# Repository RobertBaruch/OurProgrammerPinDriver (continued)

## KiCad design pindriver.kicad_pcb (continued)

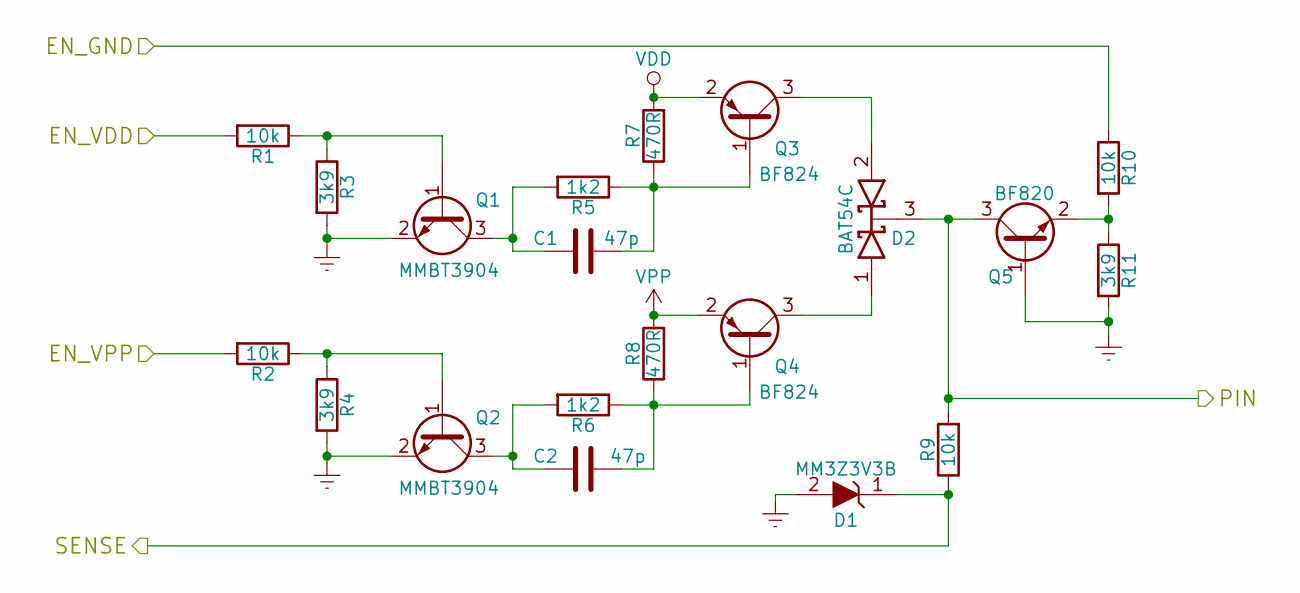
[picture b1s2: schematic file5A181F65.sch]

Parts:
C1, C2: 47p; C_0603_HandSoldering
D1: MM3Z3V3B; D_SOD-323_HandSoldering
D2: BAT54C; SOT-23_Handsoldering
Q1, Q2: MMBT3904; SOT-23_Handsoldering
Q3, Q4: BF824; SOT-23_Handsoldering
Q5: BF820; SOT-23_Handsoldering
R1, R2, R9, R10: 10k; R_0603_HandSoldering
R3, R4, R11: 3k9; R_0603_HandSoldering
R5, R6: 1k2; R_0603_HandSoldering
R7, R8: 470R; R_0603_HandSoldering

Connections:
/EN_GND36: R10.1; also elsewhere on the board
/EN_VDD36: R1.2; also elsewhere on the board
/EN_VPP36: R2.2; also elsewhere on the board
/PIN36: D2.3 (K), Q5.3 (C), R9.2; also elsewhere on the board
/SENSE36: D1.1 (K), R9.1; also elsewhere on the board
GNDREF: D1.2 (A), Q1.2 (E), Q2.2 (E), Q5.1 (B), R3.2, R4.2, R11.2; also elsewhere on the board
unnamed: C1.1, Q3.1 (B), R5.1, R7.1
unnamed: C1.2, Q1.3 (C), R5.2
unnamed: C2.1, Q4.1 (B), R6.1, R8.1
unnamed: C2.2, Q2.3 (C), R6.2
unnamed: D2.1 (A), Q4.3 (C)
unnamed: D2.2 (A), Q3.3 (C)
unnamed: Q1.1 (B), R1.1, R3.1
unnamed: Q2.1 (B), R2.1, R4.1
unnamed: Q5.2 (E), R10.2, R11.1
VDD: Q3.2 (E), R7.2; also elsewhere on the board
VPP: Q4.2 (E), R8.2; also elsewhere on the board

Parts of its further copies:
C3, C4, C5, C6, C7, C8, C9, C10, C11, C12, C13, C14, C15, C16, C17, C18, C19, C20, C21, C22, C23, C24, C25, C26, C27, C28, C29, C30, C31, C32, C33, C34, C35, C36, C37, C38, C39, C40, C41, C42, C43, C44, C45, C46, C47, C48, C49, C50, C51, C52, C53, C54, C55, C56, C57, C58, C59, C60, C61, C62, C63, C64, C65, C66, C67, C68, C69, C70, C71, C72, C73, C74, C75, C76, C77, C78, C79, C80: 47p; C_0603_HandSoldering
D3, D5, D7, D9, D11, D13, D15, D17, D19, D21, D23, D25, D27, D29, D31, D33, D35, D37, D39, D41, D43, D45, D47, D49, D51, D53, D55, D57, D59, D61, D63, D65, D67, D69, D71, D73, D75, D77, D79: MM3Z3V3B; D_SOD-323_HandSoldering
D4, D6, D8, D10, D12, D14, D16, D18, D20, D22, D24, D26, D28, D30, D32, D34, D36, D38, D40, D42, D44, D46, D48, D50, D52, D54, D56, D58, D60, D62, D64, D66, D68, D70, D72, D74, D76, D78, D80: BAT54C; SOT-23_Handsoldering
Q6, Q7, Q11, Q12, Q16, Q17, Q21, Q22, Q26, Q27, Q31, Q32, Q36, Q37, Q41, Q42, Q46, Q47, Q51, Q52, Q56, Q57, Q61, Q62, Q66, Q67, Q71, Q72, Q76, Q77, Q81, Q82, Q86, Q87, Q91, Q92, Q96, Q97, Q101, Q102, Q106, Q107, Q111, Q112, Q116, Q117, Q121, Q122, Q126, Q127, Q131, Q132, Q136, Q137, Q141, Q142, Q146, Q147, Q151, Q152, Q156, Q157, Q161, Q162, Q166, Q167, Q171, Q172, Q176, Q177, Q181, Q182, Q186, Q187, Q191, Q192, Q196, Q197: MMBT3904; SOT-23_Handsoldering
Q8, Q9, Q13, Q14, Q18, Q19, Q23, Q24, Q28, Q29, Q33, Q34, Q38, Q39, Q43, Q44, Q48, Q49, Q53, Q54, Q58, Q59, Q63, Q64, Q68, Q69, Q73, Q74, Q78, Q79, Q83, Q84, Q88, Q89, Q93, Q94, Q98, Q99, Q103, Q104, Q108, Q109, Q113, Q114, Q118, Q119, Q123, Q124, Q128, Q129, Q133, Q134, Q138, Q139, Q143, Q144, Q148, Q149, Q153, Q154, Q158, Q159, Q163, Q164, Q168, Q169, Q173, Q174, Q178, Q179, Q183, Q184, Q188, Q189, Q193, Q194, Q198, Q199: BF824; SOT-23_Handsoldering
Q10, Q15, Q20, Q25, Q30, Q35, Q40, Q45, Q50, Q55, Q60, Q65, Q70, Q75, Q80, Q85, Q90, Q95, Q100, Q105, Q110, Q115, Q120, Q125, Q130, Q135, Q140, Q145, Q150, Q155, Q160, Q165, Q170, Q175, Q180, Q185, Q190, Q195, Q200: BF820; SOT-23_Handsoldering
R12, R13, R20, R21, R23, R24, R31, R32, R34, R35, R42, R43, R45, R46, R53, R54, R56, R57, R64, R65, R67, R68, R75, R76, R78, R79, R86, R87, R89, R90, R97, R98, R100, R101, R108, R109, R111, R112, R119, R120, R122, R123, R130, R131, R133, R134, R141, R142, R144, R145, R152, R153, R155, R156, R163, R164, R166, R167, R174, R175, R177, R178, R185, R186, R188, R189, R196, R197, R199, R200, R207, R208, R210, R211, R218, R219, R221, R222, R229, R230, R232, R233, R240, R241, R243, R244, R251, R252, R254, R255, R262, R263, R265, R266, R273, R274, R276, R277, R284, R285, R287, R288, R295, R296, R298, R299, R306, R307, R309, R310, R317, R318, R320, R321, R328, R329, R331, R332, R339, R340, R342, R343, R350, R351, R353, R354, R361, R362, R364, R365, R372, R373, R375, R376, R383, R384, R386, R387, R394, R395, R397, R398, R405, R406, R408, R409, R416, R417, R419, R420, R427, R428, R430, R431, R438, R439: 10k; R_0603_HandSoldering
R14, R15, R22, R25, R26, R33, R36, R37, R44, R47, R48, R55, R58, R59, R66, R69, R70, R77, R80, R81, R88, R91, R92, R99, R102, R103, R110, R113, R114, R121, R124, R125, R132, R135, R136, R143, R146, R147, R154, R157, R158, R165, R168, R169, R176, R179, R180, R187, R190, R191, R198, R201, R202, R209, R212, R213, R220, R223, R224, R231, R234, R235, R242, R245, R246, R253, R256, R257, R264, R267, R268, R275, R278, R279, R286, R289, R290, R297, R300, R301, R308, R311, R312, R319, R322, R323, R330, R333, R334, R341, R344, R345, R352, R355, R356, R363, R366, R367, R374, R377, R378, R385, R388, R389, R396, R399, R400, R407, R410, R411, R418, R421, R422, R429, R432, R433, R440: 3k9; R_0603_HandSoldering
R16, R17, R27, R28, R38, R39, R49, R50, R60, R61, R71, R72, R82, R83, R93, R94, R104, R105, R115, R116, R126, R127, R137, R138, R148, R149, R159, R160, R170, R171, R181, R182, R192, R193, R203, R204, R214, R215, R225, R226, R236, R237, R247, R248, R258, R259, R269, R270, R280, R281, R291, R292, R302, R303, R313, R314, R324, R325, R335, R336, R346, R347, R357, R358, R368, R369, R379, R380, R390, R391, R401, R402, R412, R413, R423, R424, R434, R435: 1k2; R_0603_HandSoldering
R18, R19, R29, R30, R40, R41, R51, R52, R62, R63, R73, R74, R84, R85, R95, R96, R106, R107, R117, R118, R128, R129, R139, R140, R150, R151, R161, R162, R172, R173, R183, R184, R194, R195, R205, R206, R216, R217, R227, R228, R238, R239, R249, R250, R260, R261, R271, R272, R282, R283, R293, R294, R304, R305, R315, R316, R326, R327, R337, R338, R348, R349, R359, R360, R370, R371, R381, R382, R392, R393, R403, R404, R414, R415, R425, R426, R436, R437: 470R; R_0603_HandSoldering

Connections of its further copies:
/EN_GND1: R395.1; also elsewhere on the board
/EN_GND2: R406.1; also elsewhere on the board
/EN_GND3: R417.1; also elsewhere on the board
/EN_GND4: R428.1; also elsewhere on the board
/EN_GND5: R439.1; also elsewhere on the board
/EN_GND6: R340.1; also elsewhere on the board
/EN_GND7: R351.1; also elsewhere on the board
/EN_GND8: R362.1; also elsewhere on the board
/EN_GND9: R373.1; also elsewhere on the board
/EN_GND10: R384.1; also elsewhere on the board
/EN_GND11: R285.1; also elsewhere on the board
/EN_GND12: R296.1; also elsewhere on the board
/EN_GND13: R307.1; also elsewhere on the board
/EN_GND14: R318.1; also elsewhere on the board
/EN_GND15: R329.1; also elsewhere on the board
/EN_GND16: R230.1; also elsewhere on the board
/EN_GND17: R241.1; also elsewhere on the board
/EN_GND18: R252.1; also elsewhere on the board
/EN_GND19: R263.1; also elsewhere on the board
/EN_GND20: R274.1; also elsewhere on the board
/EN_GND21: R175.1; also elsewhere on the board
/EN_GND22: R186.1; also elsewhere on the board
/EN_GND23: R197.1; also elsewhere on the board
/EN_GND24: R208.1; also elsewhere on the board
/EN_GND25: R219.1; also elsewhere on the board
/EN_GND26: R120.1; also elsewhere on the board
/EN_GND27: R131.1; also elsewhere on the board
/EN_GND28: R142.1; also elsewhere on the board
/EN_GND29: R153.1; also elsewhere on the board
/EN_GND30: R164.1; also elsewhere on the board
/EN_GND31: R65.1; also elsewhere on the board
/EN_GND32: R76.1; also elsewhere on the board
/EN_GND33: R87.1; also elsewhere on the board
/EN_GND34: R98.1; also elsewhere on the board
/EN_GND35: R109.1; also elsewhere on the board
/EN_GND37: R21.1; also elsewhere on the board
/EN_GND38: R32.1; also elsewhere on the board
/EN_GND39: R43.1; also elsewhere on the board
/EN_GND40: R54.1; also elsewhere on the board
/EN_VDD1: R386.2; also elsewhere on the board
/EN_VDD2: R397.2; also elsewhere on the board
/EN_VDD3: R408.2; also elsewhere on the board
/EN_VDD4: R419.2; also elsewhere on the board
/EN_VDD5: R430.2; also elsewhere on the board
/EN_VDD6: R331.2; also elsewhere on the board
/EN_VDD7: R342.2; also elsewhere on the board
/EN_VDD8: R353.2; also elsewhere on the board
/EN_VDD9: R364.2; also elsewhere on the board
/EN_VDD10: R375.2; also elsewhere on the board
/EN_VDD11: R276.2; also elsewhere on the board
/EN_VDD12: R287.2; also elsewhere on the board
/EN_VDD13: R298.2; also elsewhere on the board
/EN_VDD14: R309.2; also elsewhere on the board
/EN_VDD15: R320.2; also elsewhere on the board
/EN_VDD16: R221.2; also elsewhere on the board
/EN_VDD17: R232.2; also elsewhere on the board
/EN_VDD18: R243.2; also elsewhere on the board
/EN_VDD19: R254.2; also elsewhere on the board
/EN_VDD20: R265.2; also elsewhere on the board
/EN_VDD21: R166.2; also elsewhere on the board
/EN_VDD22: R177.2; also elsewhere on the board
/EN_VDD23: R188.2; also elsewhere on the board
/EN_VDD24: R199.2; also elsewhere on the board
/EN_VDD25: R210.2; also elsewhere on the board
/EN_VDD26: R111.2; also elsewhere on the board
/EN_VDD27: R122.2; also elsewhere on the board
/EN_VDD28: R133.2; also elsewhere on the board
/EN_VDD29: R144.2; also elsewhere on the board
/EN_VDD30: R155.2; also elsewhere on the board
/EN_VDD31: R56.2; also elsewhere on the board
/EN_VDD32: R67.2; also elsewhere on the board
/EN_VDD33: R78.2; also elsewhere on the board
/EN_VDD34: R89.2; also elsewhere on the board
/EN_VDD35: R100.2; also elsewhere on the board
/EN_VDD37: R12.2; also elsewhere on the board
/EN_VDD38: R23.2; also elsewhere on the board
/EN_VDD39: R34.2; also elsewhere on the board
/EN_VDD40: R45.2; also elsewhere on the board
/EN_VPP1: R387.2; also elsewhere on the board
/EN_VPP2: R398.2; also elsewhere on the board
/EN_VPP3: R409.2; also elsewhere on the board
/EN_VPP4: R420.2; also elsewhere on the board
/EN_VPP5: R431.2; also elsewhere on the board
/EN_VPP6: R332.2; also elsewhere on the board
/EN_VPP7: R343.2; also elsewhere on the board
/EN_VPP8: R354.2; also elsewhere on the board
/EN_VPP9: R365.2; also elsewhere on the board
/EN_VPP10: R376.2; also elsewhere on the board
/EN_VPP11: R277.2; also elsewhere on the board
/EN_VPP12: R288.2; also elsewhere on the board
/EN_VPP13: R299.2; also elsewhere on the board
/EN_VPP14: R310.2; also elsewhere on the board
/EN_VPP15: R321.2; also elsewhere on the board
/EN_VPP16: R222.2; also elsewhere on the board
/EN_VPP17: R233.2; also elsewhere on the board
/EN_VPP18: R244.2; also elsewhere on the board
/EN_VPP19: R255.2; also elsewhere on the board
/EN_VPP20: R266.2; also elsewhere on the board
/EN_VPP21: R167.2; also elsewhere on the board
/EN_VPP22: R178.2; also elsewhere on the board
/EN_VPP23: R189.2; also elsewhere on the board
/EN_VPP24: R200.2; also elsewhere on the board
/EN_VPP25: R211.2; also elsewhere on the board
/EN_VPP26: R112.2; also elsewhere on the board
/EN_VPP27: R123.2; also elsewhere on the board
/EN_VPP28: R134.2; also elsewhere on the board
/EN_VPP29: R145.2; also elsewhere on the board
/EN_VPP30: R156.2; also elsewhere on the board
/EN_VPP31: R57.2; also elsewhere on the board
/EN_VPP32: R68.2; also elsewhere on the board
/EN_VPP33: R79.2; also elsewhere on the board
/EN_VPP34: R90.2; also elsewhere on the board
/EN_VPP35: R101.2; also elsewhere on the board
/EN_VPP37: R13.2; also elsewhere on the board
/EN_VPP38: R24.2; also elsewhere on the board
/EN_VPP39: R35.2; also elsewhere on the board
/EN_VPP40: R46.2; also elsewhere on the board
/PIN1: D72.3 (K), Q180.3 (C), R394.2; also elsewhere on the board
/PIN2: D74.3 (K), Q185.3 (C), R405.2; also elsewhere on the board
/PIN3: D76.3 (K), Q190.3 (C), R416.2; also elsewhere on the board
/PIN4: D78.3 (K), Q195.3 (C), R427.2; also elsewhere on the board
/PIN5: D80.3 (K), Q200.3 (C), R438.2; also elsewhere on the board
/PIN6: D62.3 (K), Q155.3 (C), R339.2; also elsewhere on the board
/PIN7: D64.3 (K), Q160.3 (C), R350.2; also elsewhere on the board
/PIN8: D66.3 (K), Q165.3 (C), R361.2; also elsewhere on the board
/PIN9: D68.3 (K), Q170.3 (C), R372.2; also elsewhere on the board
/PIN10: D70.3 (K), Q175.3 (C), R383.2; also elsewhere on the board
/PIN11: D52.3 (K), Q130.3 (C), R284.2; also elsewhere on the board
/PIN12: D54.3 (K), Q135.3 (C), R295.2; also elsewhere on the board
/PIN13: D56.3 (K), Q140.3 (C), R306.2; also elsewhere on the board
/PIN14: D58.3 (K), Q145.3 (C), R317.2; also elsewhere on the board
/PIN15: D60.3 (K), Q150.3 (C), R328.2; also elsewhere on the board
/PIN16: D42.3 (K), Q105.3 (C), R229.2; also elsewhere on the board
/PIN17: D44.3 (K), Q110.3 (C), R240.2; also elsewhere on the board
/PIN18: D46.3 (K), Q115.3 (C), R251.2; also elsewhere on the board
/PIN19: D48.3 (K), Q120.3 (C), R262.2; also elsewhere on the board
/PIN20: D50.3 (K), Q125.3 (C), R273.2; also elsewhere on the board
/PIN21: D32.3 (K), Q80.3 (C), R174.2; also elsewhere on the board
/PIN22: D34.3 (K), Q85.3 (C), R185.2; also elsewhere on the board
/PIN23: D36.3 (K), Q90.3 (C), R196.2; also elsewhere on the board
/PIN24: D38.3 (K), Q95.3 (C), R207.2; also elsewhere on the board
/PIN25: D40.3 (K), Q100.3 (C), R218.2; also elsewhere on the board
/PIN26: D22.3 (K), Q55.3 (C), R119.2; also elsewhere on the board
/PIN27: D24.3 (K), Q60.3 (C), R130.2; also elsewhere on the board
/PIN28: D26.3 (K), Q65.3 (C), R141.2; also elsewhere on the board
/PIN29: D28.3 (K), Q70.3 (C), R152.2; also elsewhere on the board
/PIN30: D30.3 (K), Q75.3 (C), R163.2; also elsewhere on the board
/PIN31: D12.3 (K), Q30.3 (C), R64.2; also elsewhere on the board
/PIN32: D14.3 (K), Q35.3 (C), R75.2; also elsewhere on the board
/PIN33: D16.3 (K), Q40.3 (C), R86.2; also elsewhere on the board
/PIN34: D18.3 (K), Q45.3 (C), R97.2; also elsewhere on the board
/PIN35: D20.3 (K), Q50.3 (C), R108.2; also elsewhere on the board
/PIN37: D4.3 (K), Q10.3 (C), R20.2; also elsewhere on the board
/PIN38: D6.3 (K), Q15.3 (C), R31.2; also elsewhere on the board
/PIN39: D8.3 (K), Q20.3 (C), R42.2; also elsewhere on the board
/PIN40: D10.3 (K), Q25.3 (C), R53.2; also elsewhere on the board
/SENSE1: D71.1 (K), R394.1; also elsewhere on the board
/SENSE2: D73.1 (K), R405.1; also elsewhere on the board
/SENSE3: D75.1 (K), R416.1; also elsewhere on the board
/SENSE4: D77.1 (K), R427.1; also elsewhere on the board
/SENSE5: D79.1 (K), R438.1; also elsewhere on the board
/SENSE6: D61.1 (K), R339.1; also elsewhere on the board
/SENSE7: D63.1 (K), R350.1; also elsewhere on the board
/SENSE8: D65.1 (K), R361.1; also elsewhere on the board
/SENSE9: D67.1 (K), R372.1; also elsewhere on the board
/SENSE10: D69.1 (K), R383.1; also elsewhere on the board
/SENSE11: D51.1 (K), R284.1; also elsewhere on the board
/SENSE12: D53.1 (K), R295.1; also elsewhere on the board
/SENSE13: D55.1 (K), R306.1; also elsewhere on the board
/SENSE14: D57.1 (K), R317.1; also elsewhere on the board
/SENSE15: D59.1 (K), R328.1; also elsewhere on the board
/SENSE16: D41.1 (K), R229.1; also elsewhere on the board
/SENSE17: D43.1 (K), R240.1; also elsewhere on the board
/SENSE18: D45.1 (K), R251.1; also elsewhere on the board
/SENSE19: D47.1 (K), R262.1; also elsewhere on the board
/SENSE20: D49.1 (K), R273.1; also elsewhere on the board
/SENSE21: D31.1 (K), R174.1; also elsewhere on the board
/SENSE22: D33.1 (K), R185.1; also elsewhere on the board
/SENSE23: D35.1 (K), R196.1; also elsewhere on the board
/SENSE24: D37.1 (K), R207.1; also elsewhere on the board
/SENSE25: D39.1 (K), R218.1; also elsewhere on the board
/SENSE26: D21.1 (K), R119.1; also elsewhere on the board
/SENSE27: D23.1 (K), R130.1; also elsewhere on the board
/SENSE28: D25.1 (K), R141.1; also elsewhere on the board
/SENSE29: D27.1 (K), R152.1; also elsewhere on the board
/SENSE30: D29.1 (K), R163.1; also elsewhere on the board
/SENSE31: D11.1 (K), R64.1; also elsewhere on the board
/SENSE32: D13.1 (K), R75.1; also elsewhere on the board
/SENSE33: D15.1 (K), R86.1; also elsewhere on the board
/SENSE34: D17.1 (K), R97.1; also elsewhere on the board
/SENSE35: D19.1 (K), R108.1; also elsewhere on the board
/SENSE37: D3.1 (K), R20.1; also elsewhere on the board
/SENSE38: D5.1 (K), R31.1; also elsewhere on the board
/SENSE39: D7.1 (K), R42.1; also elsewhere on the board
/SENSE40: D9.1 (K), R53.1; also elsewhere on the board
GNDREF: D3.2 (A), D5.2 (A), D7.2 (A), D9.2 (A), D11.2 (A), D13.2 (A), D15.2 (A), D17.2 (A), D19.2 (A), D21.2 (A), D23.2 (A), D25.2 (A), D27.2 (A), D29.2 (A), D31.2 (A), D33.2 (A), D35.2 (A), D37.2 (A), D39.2 (A), D41.2 (A), D43.2 (A), D45.2 (A), D47.2 (A), D49.2 (A), D51.2 (A), D53.2 (A), D55.2 (A), D57.2 (A), D59.2 (A), D61.2 (A), D63.2 (A), D65.2 (A), D67.2 (A), D69.2 (A), D71.2 (A), D73.2 (A), D75.2 (A), D77.2 (A), D79.2 (A), Q6.2 (E), Q7.2 (E), Q10.1 (B), Q11.2 (E), Q12.2 (E), Q15.1 (B), Q16.2 (E), Q17.2 (E), Q20.1 (B), Q21.2 (E), Q22.2 (E), Q25.1 (B), Q26.2 (E), Q27.2 (E), Q30.1 (B), Q31.2 (E), Q32.2 (E), Q35.1 (B), Q36.2 (E), Q37.2 (E), Q40.1 (B), Q41.2 (E), Q42.2 (E), Q45.1 (B), Q46.2 (E), Q47.2 (E), Q50.1 (B), Q51.2 (E), Q52.2 (E), Q55.1 (B), Q56.2 (E), Q57.2 (E), Q60.1 (B), Q61.2 (E), Q62.2 (E), Q65.1 (B), Q66.2 (E), Q67.2 (E), Q70.1 (B), Q71.2 (E), Q72.2 (E), Q75.1 (B), Q76.2 (E), Q77.2 (E), Q80.1 (B), Q81.2 (E), Q82.2 (E), Q85.1 (B), Q86.2 (E), Q87.2 (E), Q90.1 (B), Q91.2 (E), Q92.2 (E), Q95.1 (B), Q96.2 (E), Q97.2 (E), Q100.1 (B), Q101.2 (E), Q102.2 (E), Q105.1 (B), Q106.2 (E), Q107.2 (E), Q110.1 (B), Q111.2 (E), Q112.2 (E), Q115.1 (B), Q116.2 (E), Q117.2 (E), Q120.1 (B), Q121.2 (E), Q122.2 (E), Q125.1 (B), Q126.2 (E), Q127.2 (E), Q130.1 (B), Q131.2 (E), Q132.2 (E), Q135.1 (B), Q136.2 (E), Q137.2 (E), Q140.1 (B), Q141.2 (E), Q142.2 (E), Q145.1 (B), Q146.2 (E), Q147.2 (E), Q150.1 (B), Q151.2 (E), Q152.2 (E), Q155.1 (B), Q156.2 (E), Q157.2 (E), Q160.1 (B), Q161.2 (E), Q162.2 (E), Q165.1 (B), Q166.2 (E), Q167.2 (E), Q170.1 (B), Q171.2 (E), Q172.2 (E), Q175.1 (B), Q176.2 (E), Q177.2 (E), Q180.1 (B), Q181.2 (E), Q182.2 (E), Q185.1 (B), Q186.2 (E), Q187.2 (E), Q190.1 (B), Q191.2 (E), Q192.2 (E), Q195.1 (B), Q196.2 (E), Q197.2 (E), Q200.1 (B), R14.2, R15.2, R22.2, R25.2, R26.2, R33.2, R36.2, R37.2, R44.2, R47.2, R48.2, R55.2, R58.2, R59.2, R66.2, R69.2, R70.2, R77.2, R80.2, R81.2, R88.2, R91.2, R92.2, R99.2, R102.2, R103.2, R110.2, R113.2, R114.2, R121.2, R124.2, R125.2, R132.2, R135.2, R136.2, R143.2, R146.2, R147.2, R154.2, R157.2, R158.2, R165.2, R168.2, R169.2, R176.2, R179.2, R180.2, R187.2, R190.2, R191.2, R198.2, R201.2, R202.2, R209.2, R212.2, R213.2, R220.2, R223.2, R224.2, R231.2, R234.2, R235.2, R242.2, R245.2, R246.2, R253.2, R256.2, R257.2, R264.2, R267.2, R268.2, R275.2, R278.2, R279.2, R286.2, R289.2, R290.2, R297.2, R300.2, R301.2, R308.2, R311.2, R312.2, R319.2, R322.2, R323.2, R330.2, R333.2, R334.2, R341.2, R344.2, R345.2, R352.2, R355.2, R356.2, R363.2, R366.2, R367.2, R374.2, R377.2, R378.2, R385.2, R388.2, R389.2, R396.2, R399.2, R400.2, R407.2, R410.2, R411.2, R418.2, R421.2, R422.2, R429.2, R432.2, R433.2, R440.2; also elsewhere on the board
unnamed: C3.1, Q8.1 (B), R16.1, R18.1
unnamed: C3.2, Q6.3 (C), R16.2
unnamed: C4.1, Q9.1 (B), R17.1, R19.1
unnamed: C4.2, Q7.3 (C), R17.2
unnamed: C5.1, Q13.1 (B), R27.1, R29.1
unnamed: C5.2, Q11.3 (C), R27.2
unnamed: C6.1, Q14.1 (B), R28.1, R30.1
unnamed: C6.2, Q12.3 (C), R28.2
unnamed: C7.1, Q18.1 (B), R38.1, R40.1
unnamed: C7.2, Q16.3 (C), R38.2
unnamed: C8.1, Q19.1 (B), R39.1, R41.1
unnamed: C8.2, Q17.3 (C), R39.2
unnamed: C9.1, Q23.1 (B), R49.1, R51.1
unnamed: C9.2, Q21.3 (C), R49.2
unnamed: C10.1, Q24.1 (B), R50.1, R52.1
unnamed: C10.2, Q22.3 (C), R50.2
unnamed: C11.1, Q28.1 (B), R60.1, R62.1
unnamed: C11.2, Q26.3 (C), R60.2
unnamed: C12.1, Q29.1 (B), R61.1, R63.1
unnamed: C12.2, Q27.3 (C), R61.2
unnamed: C13.1, Q33.1 (B), R71.1, R73.1
unnamed: C13.2, Q31.3 (C), R71.2
unnamed: C14.1, Q34.1 (B), R72.1, R74.1
unnamed: C14.2, Q32.3 (C), R72.2
unnamed: C15.1, Q38.1 (B), R82.1, R84.1
unnamed: C15.2, Q36.3 (C), R82.2
unnamed: C16.1, Q39.1 (B), R83.1, R85.1
unnamed: C16.2, Q37.3 (C), R83.2
unnamed: C17.1, Q43.1 (B), R93.1, R95.1
unnamed: C17.2, Q41.3 (C), R93.2
unnamed: C18.1, Q44.1 (B), R94.1, R96.1
unnamed: C18.2, Q42.3 (C), R94.2
unnamed: C19.1, Q48.1 (B), R104.1, R106.1
unnamed: C19.2, Q46.3 (C), R104.2
unnamed: C20.1, Q49.1 (B), R105.1, R107.1
unnamed: C20.2, Q47.3 (C), R105.2
unnamed: C21.1, Q53.1 (B), R115.1, R117.1
unnamed: C21.2, Q51.3 (C), R115.2
unnamed: C22.1, Q54.1 (B), R116.1, R118.1
unnamed: C22.2, Q52.3 (C), R116.2
unnamed: C23.1, Q58.1 (B), R126.1, R128.1
unnamed: C23.2, Q56.3 (C), R126.2
unnamed: C24.1, Q59.1 (B), R127.1, R129.1
unnamed: C24.2, Q57.3 (C), R127.2
unnamed: C25.1, Q63.1 (B), R137.1, R139.1
unnamed: C25.2, Q61.3 (C), R137.2
unnamed: C26.1, Q64.1 (B), R138.1, R140.1
unnamed: C26.2, Q62.3 (C), R138.2
unnamed: C27.1, Q68.1 (B), R148.1, R150.1
unnamed: C27.2, Q66.3 (C), R148.2
unnamed: C28.1, Q69.1 (B), R149.1, R151.1
unnamed: C28.2, Q67.3 (C), R149.2
unnamed: C29.1, Q73.1 (B), R159.1, R161.1
unnamed: C29.2, Q71.3 (C), R159.2
unnamed: C30.1, Q74.1 (B), R160.1, R162.1
unnamed: C30.2, Q72.3 (C), R160.2
unnamed: C31.1, Q78.1 (B), R170.1, R172.1
unnamed: C31.2, Q76.3 (C), R170.2
unnamed: C32.1, Q79.1 (B), R171.1, R173.1
unnamed: C32.2, Q77.3 (C), R171.2
unnamed: C33.1, Q83.1 (B), R181.1, R183.1
unnamed: C33.2, Q81.3 (C), R181.2
unnamed: C34.1, Q84.1 (B), R182.1, R184.1
unnamed: C34.2, Q82.3 (C), R182.2
unnamed: C35.1, Q88.1 (B), R192.1, R194.1
unnamed: C35.2, Q86.3 (C), R192.2
unnamed: C36.1, Q89.1 (B), R193.1, R195.1
unnamed: C36.2, Q87.3 (C), R193.2
unnamed: C37.1, Q93.1 (B), R203.1, R205.1
unnamed: C37.2, Q91.3 (C), R203.2
unnamed: C38.1, Q94.1 (B), R204.1, R206.1
unnamed: C38.2, Q92.3 (C), R204.2
unnamed: C39.1, Q98.1 (B), R214.1, R216.1
unnamed: C39.2, Q96.3 (C), R214.2
unnamed: C40.1, Q99.1 (B), R215.1, R217.1
unnamed: C40.2, Q97.3 (C), R215.2
unnamed: C41.1, Q103.1 (B), R225.1, R227.1
unnamed: C41.2, Q101.3 (C), R225.2
unnamed: C42.1, Q104.1 (B), R226.1, R228.1
unnamed: C42.2, Q102.3 (C), R226.2
unnamed: C43.1, Q108.1 (B), R236.1, R238.1
unnamed: C43.2, Q106.3 (C), R236.2
unnamed: C44.1, Q109.1 (B), R237.1, R239.1
unnamed: C44.2, Q107.3 (C), R237.2
unnamed: C45.1, Q113.1 (B), R247.1, R249.1
unnamed: C45.2, Q111.3 (C), R247.2
unnamed: C46.1, Q114.1 (B), R248.1, R250.1
unnamed: C46.2, Q112.3 (C), R248.2
unnamed: C47.1, Q118.1 (B), R258.1, R260.1
unnamed: C47.2, Q116.3 (C), R258.2
unnamed: C48.1, Q119.1 (B), R259.1, R261.1
unnamed: C48.2, Q117.3 (C), R259.2
unnamed: C49.1, Q123.1 (B), R269.1, R271.1
unnamed: C49.2, Q121.3 (C), R269.2
unnamed: C50.1, Q124.1 (B), R270.1, R272.1
unnamed: C50.2, Q122.3 (C), R270.2
unnamed: C51.1, Q128.1 (B), R280.1, R282.1
unnamed: C51.2, Q126.3 (C), R280.2
unnamed: C52.1, Q129.1 (B), R281.1, R283.1
unnamed: C52.2, Q127.3 (C), R281.2
unnamed: C53.1, Q133.1 (B), R291.1, R293.1
unnamed: C53.2, Q131.3 (C), R291.2
unnamed: C54.1, Q134.1 (B), R292.1, R294.1
unnamed: C54.2, Q132.3 (C), R292.2
unnamed: C55.1, Q138.1 (B), R302.1, R304.1
unnamed: C55.2, Q136.3 (C), R302.2
unnamed: C56.1, Q139.1 (B), R303.1, R305.1
unnamed: C56.2, Q137.3 (C), R303.2
unnamed: C57.1, Q143.1 (B), R313.1, R315.1
unnamed: C57.2, Q141.3 (C), R313.2
unnamed: C58.1, Q144.1 (B), R314.1, R316.1
unnamed: C58.2, Q142.3 (C), R314.2
unnamed: C59.1, Q148.1 (B), R324.1, R326.1
unnamed: C59.2, Q146.3 (C), R324.2
unnamed: C60.1, Q149.1 (B), R325.1, R327.1
unnamed: C60.2, Q147.3 (C), R325.2
unnamed: C61.1, Q153.1 (B), R335.1, R337.1
unnamed: C61.2, Q151.3 (C), R335.2
unnamed: C62.1, Q154.1 (B), R336.1, R338.1
unnamed: C62.2, Q152.3 (C), R336.2
unnamed: C63.1, Q158.1 (B), R346.1, R348.1
unnamed: C63.2, Q156.3 (C), R346.2
unnamed: C64.1, Q159.1 (B), R347.1, R349.1
unnamed: C64.2, Q157.3 (C), R347.2
unnamed: C65.1, Q163.1 (B), R357.1, R359.1
unnamed: C65.2, Q161.3 (C), R357.2
unnamed: C66.1, Q164.1 (B), R358.1, R360.1
unnamed: C66.2, Q162.3 (C), R358.2
unnamed: C67.1, Q168.1 (B), R368.1, R370.1
unnamed: C67.2, Q166.3 (C), R368.2
unnamed: C68.1, Q169.1 (B), R369.1, R371.1
unnamed: C68.2, Q167.3 (C), R369.2
unnamed: C69.1, Q173.1 (B), R379.1, R381.1
unnamed: C69.2, Q171.3 (C), R379.2
unnamed: C70.1, Q174.1 (B), R380.1, R382.1
unnamed: C70.2, Q172.3 (C), R380.2
unnamed: C71.1, Q178.1 (B), R390.1, R392.1
unnamed: C71.2, Q176.3 (C), R390.2
unnamed: C72.1, Q179.1 (B), R391.1, R393.1
unnamed: C72.2, Q177.3 (C), R391.2
unnamed: C73.1, Q183.1 (B), R401.1, R403.1
unnamed: C73.2, Q181.3 (C), R401.2
unnamed: C74.1, Q184.1 (B), R402.1, R404.1
unnamed: C74.2, Q182.3 (C), R402.2
unnamed: C75.1, Q188.1 (B), R412.1, R414.1
unnamed: C75.2, Q186.3 (C), R412.2
unnamed: C76.1, Q189.1 (B), R413.1, R415.1
unnamed: C76.2, Q187.3 (C), R413.2
unnamed: C77.1, Q193.1 (B), R423.1, R425.1
unnamed: C77.2, Q191.3 (C), R423.2
unnamed: C78.1, Q194.1 (B), R424.1, R426.1
unnamed: C78.2, Q192.3 (C), R424.2
unnamed: C79.1, Q198.1 (B), R434.1, R436.1
unnamed: C79.2, Q196.3 (C), R434.2
unnamed: C80.1, Q199.1 (B), R435.1, R437.1
unnamed: C80.2, Q197.3 (C), R435.2
unnamed: D4.1 (A), Q9.3 (C)
unnamed: D4.2 (A), Q8.3 (C)
unnamed: D6.1 (A), Q14.3 (C)
unnamed: D6.2 (A), Q13.3 (C)
unnamed: D8.1 (A), Q19.3 (C)
unnamed: D8.2 (A), Q18.3 (C)
unnamed: D10.1 (A), Q24.3 (C)
unnamed: D10.2 (A), Q23.3 (C)
unnamed: D12.1 (A), Q29.3 (C)
unnamed: D12.2 (A), Q28.3 (C)
unnamed: D14.1 (A), Q34.3 (C)
unnamed: D14.2 (A), Q33.3 (C)
unnamed: D16.1 (A), Q39.3 (C)
unnamed: D16.2 (A), Q38.3 (C)
unnamed: D18.1 (A), Q44.3 (C)
unnamed: D18.2 (A), Q43.3 (C)
unnamed: D20.1 (A), Q49.3 (C)
unnamed: D20.2 (A), Q48.3 (C)
unnamed: D22.1 (A), Q54.3 (C)
unnamed: D22.2 (A), Q53.3 (C)
unnamed: D24.1 (A), Q59.3 (C)
unnamed: D24.2 (A), Q58.3 (C)
unnamed: D26.1 (A), Q64.3 (C)
unnamed: D26.2 (A), Q63.3 (C)
unnamed: D28.1 (A), Q69.3 (C)
unnamed: D28.2 (A), Q68.3 (C)
unnamed: D30.1 (A), Q74.3 (C)
unnamed: D30.2 (A), Q73.3 (C)
unnamed: D32.1 (A), Q79.3 (C)
unnamed: D32.2 (A), Q78.3 (C)
unnamed: D34.1 (A), Q84.3 (C)
unnamed: D34.2 (A), Q83.3 (C)
unnamed: D36.1 (A), Q89.3 (C)
unnamed: D36.2 (A), Q88.3 (C)
unnamed: D38.1 (A), Q94.3 (C)
unnamed: D38.2 (A), Q93.3 (C)
unnamed: D40.1 (A), Q99.3 (C)
unnamed: D40.2 (A), Q98.3 (C)
unnamed: D42.1 (A), Q104.3 (C)
unnamed: D42.2 (A), Q103.3 (C)
unnamed: D44.1 (A), Q109.3 (C)
unnamed: D44.2 (A), Q108.3 (C)
unnamed: D46.1 (A), Q114.3 (C)
unnamed: D46.2 (A), Q113.3 (C)
unnamed: D48.1 (A), Q119.3 (C)
unnamed: D48.2 (A), Q118.3 (C)
unnamed: D50.1 (A), Q124.3 (C)
unnamed: D50.2 (A), Q123.3 (C)
unnamed: D52.1 (A), Q129.3 (C)
unnamed: D52.2 (A), Q128.3 (C)
unnamed: D54.1 (A), Q134.3 (C)
unnamed: D54.2 (A), Q133.3 (C)
unnamed: D56.1 (A), Q139.3 (C)
unnamed: D56.2 (A), Q138.3 (C)
unnamed: D58.1 (A), Q144.3 (C)
unnamed: D58.2 (A), Q143.3 (C)
unnamed: D60.1 (A), Q149.3 (C)
unnamed: D60.2 (A), Q148.3 (C)
unnamed: D62.1 (A), Q154.3 (C)
unnamed: D62.2 (A), Q153.3 (C)
unnamed: D64.1 (A), Q159.3 (C)
unnamed: D64.2 (A), Q158.3 (C)
unnamed: D66.1 (A), Q164.3 (C)
unnamed: D66.2 (A), Q163.3 (C)
unnamed: D68.1 (A), Q169.3 (C)
unnamed: D68.2 (A), Q168.3 (C)
unnamed: D70.1 (A), Q174.3 (C)
unnamed: D70.2 (A), Q173.3 (C)
unnamed: D72.1 (A), Q179.3 (C)
unnamed: D72.2 (A), Q178.3 (C)
unnamed: D74.1 (A), Q184.3 (C)
unnamed: D74.2 (A), Q183.3 (C)
unnamed: D76.1 (A), Q189.3 (C)
unnamed: D76.2 (A), Q188.3 (C)
unnamed: D78.1 (A), Q194.3 (C)
unnamed: D78.2 (A), Q193.3 (C)
unnamed: D80.1 (A), Q199.3 (C)
unnamed: D80.2 (A), Q198.3 (C)
unnamed: Q6.1 (B), R12.1, R14.1
unnamed: Q7.1 (B), R13.1, R15.1
unnamed: Q10.2 (E), R21.2, R22.1
unnamed: Q11.1 (B), R23.1, R25.1
unnamed: Q12.1 (B), R24.1, R26.1
unnamed: Q15.2 (E), R32.2, R33.1
unnamed: Q16.1 (B), R34.1, R36.1
unnamed: Q17.1 (B), R35.1, R37.1
unnamed: Q20.2 (E), R43.2, R44.1
unnamed: Q21.1 (B), R45.1, R47.1
unnamed: Q22.1 (B), R46.1, R48.1
unnamed: Q25.2 (E), R54.2, R55.1
unnamed: Q26.1 (B), R56.1, R58.1
unnamed: Q27.1 (B), R57.1, R59.1
unnamed: Q30.2 (E), R65.2, R66.1
unnamed: Q31.1 (B), R67.1, R69.1
unnamed: Q32.1 (B), R68.1, R70.1
unnamed: Q35.2 (E), R76.2, R77.1
unnamed: Q36.1 (B), R78.1, R80.1
unnamed: Q37.1 (B), R79.1, R81.1
unnamed: Q40.2 (E), R87.2, R88.1
unnamed: Q41.1 (B), R89.1, R91.1
unnamed: Q42.1 (B), R90.1, R92.1
unnamed: Q45.2 (E), R98.2, R99.1
unnamed: Q46.1 (B), R100.1, R102.1
unnamed: Q47.1 (B), R101.1, R103.1
unnamed: Q50.2 (E), R109.2, R110.1
unnamed: Q51.1 (B), R111.1, R113.1
unnamed: Q52.1 (B), R112.1, R114.1
unnamed: Q55.2 (E), R120.2, R121.1
unnamed: Q56.1 (B), R122.1, R124.1
unnamed: Q57.1 (B), R123.1, R125.1
unnamed: Q60.2 (E), R131.2, R132.1
unnamed: Q61.1 (B), R133.1, R135.1
unnamed: Q62.1 (B), R134.1, R136.1
unnamed: Q65.2 (E), R142.2, R143.1
unnamed: Q66.1 (B), R144.1, R146.1
unnamed: Q67.1 (B), R145.1, R147.1
unnamed: Q70.2 (E), R153.2, R154.1
unnamed: Q71.1 (B), R155.1, R157.1
unnamed: Q72.1 (B), R156.1, R158.1
unnamed: Q75.2 (E), R164.2, R165.1
unnamed: Q76.1 (B), R166.1, R168.1
unnamed: Q77.1 (B), R167.1, R169.1
unnamed: Q80.2 (E), R175.2, R176.1
unnamed: Q81.1 (B), R177.1, R179.1
unnamed: Q82.1 (B), R178.1, R180.1
unnamed: Q85.2 (E), R186.2, R187.1
unnamed: Q86.1 (B), R188.1, R190.1
unnamed: Q87.1 (B), R189.1, R191.1
unnamed: Q90.2 (E), R197.2, R198.1
unnamed: Q91.1 (B), R199.1, R201.1
unnamed: Q92.1 (B), R200.1, R202.1
unnamed: Q95.2 (E), R208.2, R209.1
unnamed: Q96.1 (B), R210.1, R212.1
unnamed: Q97.1 (B), R211.1, R213.1
unnamed: Q100.2 (E), R219.2, R220.1
unnamed: Q101.1 (B), R221.1, R223.1
unnamed: Q102.1 (B), R222.1, R224.1
unnamed: Q105.2 (E), R230.2, R231.1
unnamed: Q106.1 (B), R232.1, R234.1
unnamed: Q107.1 (B), R233.1, R235.1
unnamed: Q110.2 (E), R241.2, R242.1
unnamed: Q111.1 (B), R243.1, R245.1
unnamed: Q112.1 (B), R244.1, R246.1
unnamed: Q115.2 (E), R252.2, R253.1
unnamed: Q116.1 (B), R254.1, R256.1
unnamed: Q117.1 (B), R255.1, R257.1
unnamed: Q120.2 (E), R263.2, R264.1
unnamed: Q121.1 (B), R265.1, R267.1
unnamed: Q122.1 (B), R266.1, R268.1
unnamed: Q125.2 (E), R274.2, R275.1
unnamed: Q126.1 (B), R276.1, R278.1
unnamed: Q127.1 (B), R277.1, R279.1
unnamed: Q130.2 (E), R285.2, R286.1
unnamed: Q131.1 (B), R287.1, R289.1
unnamed: Q132.1 (B), R288.1, R290.1
unnamed: Q135.2 (E), R296.2, R297.1
unnamed: Q136.1 (B), R298.1, R300.1
unnamed: Q137.1 (B), R299.1, R301.1
unnamed: Q140.2 (E), R307.2, R308.1
unnamed: Q141.1 (B), R309.1, R311.1
unnamed: Q142.1 (B), R310.1, R312.1
unnamed: Q145.2 (E), R318.2, R319.1
unnamed: Q146.1 (B), R320.1, R322.1
unnamed: Q147.1 (B), R321.1, R323.1
unnamed: Q150.2 (E), R329.2, R330.1
unnamed: Q151.1 (B), R331.1, R333.1
unnamed: Q152.1 (B), R332.1, R334.1
unnamed: Q155.2 (E), R340.2, R341.1
unnamed: Q156.1 (B), R342.1, R344.1
unnamed: Q157.1 (B), R343.1, R345.1
unnamed: Q160.2 (E), R351.2, R352.1
unnamed: Q161.1 (B), R353.1, R355.1
unnamed: Q162.1 (B), R354.1, R356.1
unnamed: Q165.2 (E), R362.2, R363.1
unnamed: Q166.1 (B), R364.1, R366.1
unnamed: Q167.1 (B), R365.1, R367.1
unnamed: Q170.2 (E), R373.2, R374.1
unnamed: Q171.1 (B), R375.1, R377.1
unnamed: Q172.1 (B), R376.1, R378.1
unnamed: Q175.2 (E), R384.2, R385.1
unnamed: Q176.1 (B), R386.1, R388.1
unnamed: Q177.1 (B), R387.1, R389.1
unnamed: Q180.2 (E), R395.2, R396.1
unnamed: Q181.1 (B), R397.1, R399.1
unnamed: Q182.1 (B), R398.1, R400.1
unnamed: Q185.2 (E), R406.2, R407.1
unnamed: Q186.1 (B), R408.1, R410.1
unnamed: Q187.1 (B), R409.1, R411.1
unnamed: Q190.2 (E), R417.2, R418.1
unnamed: Q191.1 (B), R419.1, R421.1
unnamed: Q192.1 (B), R420.1, R422.1
unnamed: Q195.2 (E), R428.2, R429.1
unnamed: Q196.1 (B), R430.1, R432.1
unnamed: Q197.1 (B), R431.1, R433.1
unnamed: Q200.2 (E), R439.2, R440.1
VDD: Q8.2 (E), Q13.2 (E), Q18.2 (E), Q23.2 (E), Q28.2 (E), Q33.2 (E), Q38.2 (E), Q43.2 (E), Q48.2 (E), Q53.2 (E), Q58.2 (E), Q63.2 (E), Q68.2 (E), Q73.2 (E), Q78.2 (E), Q83.2 (E), Q88.2 (E), Q93.2 (E), Q98.2 (E), Q103.2 (E), Q108.2 (E), Q113.2 (E), Q118.2 (E), Q123.2 (E), Q128.2 (E), Q133.2 (E), Q138.2 (E), Q143.2 (E), Q148.2 (E), Q153.2 (E), Q158.2 (E), Q163.2 (E), Q168.2 (E), Q173.2 (E), Q178.2 (E), Q183.2 (E), Q188.2 (E), Q193.2 (E), Q198.2 (E), R18.2, R29.2, R40.2, R51.2, R62.2, R73.2, R84.2, R95.2, R106.2, R117.2, R128.2, R139.2, R150.2, R161.2, R172.2, R183.2, R194.2, R205.2, R216.2, R227.2, R238.2, R249.2, R260.2, R271.2, R282.2, R293.2, R304.2, R315.2, R326.2, R337.2, R348.2, R359.2, R370.2, R381.2, R392.2, R403.2, R414.2, R425.2, R436.2; also elsewhere on the board
VPP: Q9.2 (E), Q14.2 (E), Q19.2 (E), Q24.2 (E), Q29.2 (E), Q34.2 (E), Q39.2 (E), Q44.2 (E), Q49.2 (E), Q54.2 (E), Q59.2 (E), Q64.2 (E), Q69.2 (E), Q74.2 (E), Q79.2 (E), Q84.2 (E), Q89.2 (E), Q94.2 (E), Q99.2 (E), Q104.2 (E), Q109.2 (E), Q114.2 (E), Q119.2 (E), Q124.2 (E), Q129.2 (E), Q134.2 (E), Q139.2 (E), Q144.2 (E), Q149.2 (E), Q154.2 (E), Q159.2 (E), Q164.2 (E), Q169.2 (E), Q174.2 (E), Q179.2 (E), Q184.2 (E), Q189.2 (E), Q194.2 (E), Q199.2 (E), R19.2, R30.2, R41.2, R52.2, R63.2, R74.2, R85.2, R96.2, R107.2, R118.2, R129.2, R140.2, R151.2, R162.2, R173.2, R184.2, R195.2, R206.2, R217.2, R228.2, R239.2, R250.2, R261.2, R272.2, R283.2, R294.2, R305.2, R316.2, R327.2, R338.2, R349.2, R360.2, R371.2, R382.2, R393.2, R404.2, R415.2, R426.2, R437.2; also elsewhere on the board

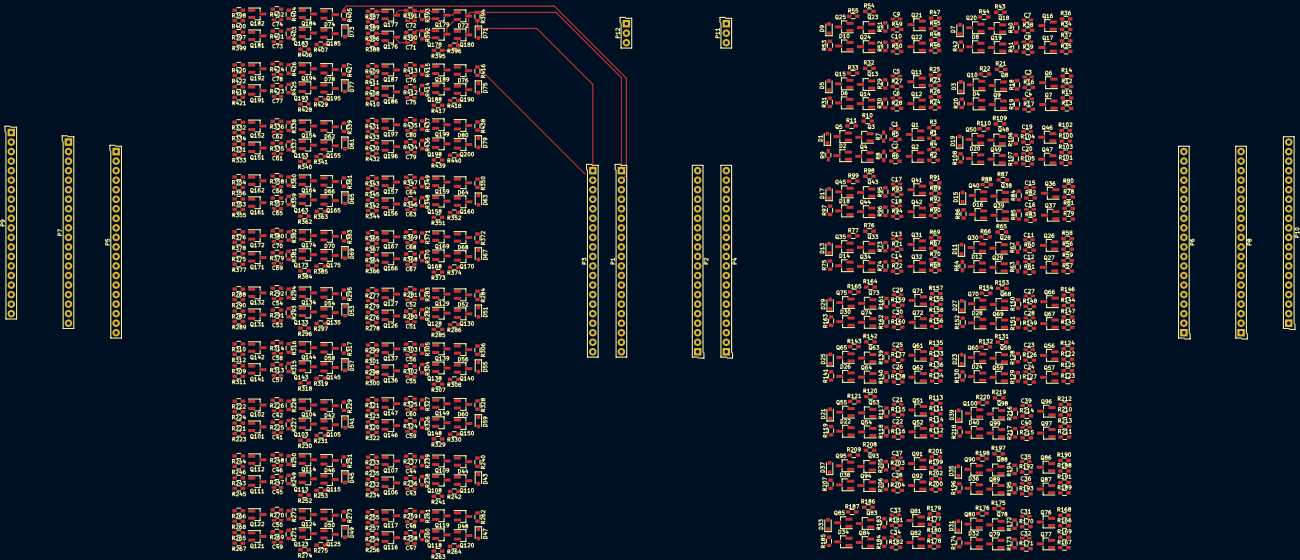
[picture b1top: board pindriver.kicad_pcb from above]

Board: 2 copper layers, 812 parts (0 on the bottom side), 563 nets.

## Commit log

2017-11-24 Adds to schematic
    Duplicates pin drivers x40, adds connectors.
2017-11-24 Adds LTSpice simulation
2017-11-24 Initial PCB
2017-11-26 Adds hacked-together PCB parser to duplicate layout, updates simulation with better circuit
